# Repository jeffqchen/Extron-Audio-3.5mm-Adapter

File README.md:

# Extron Audio 3.5mm Adapter

This is an 3.5mm audio input/output adapter for the Extron switches. It conforms to the circuit design of the official CSM6 adapter to enable correct audio levels when balanced audio is adapted to unbalanced audio through a 3.5mm jack.

-----------
## Parts

- [PCB](https://oshpark.com/shared_projects/oJI7PVwu)

- Terminal Plug - 5 pin, 3.5mm pitch, right angle, through-hole - [Link](https://github.com/jeffqchen/JeffParts/blob/main/Connectors/Phoenix%20Terminal%20Connector/Female%20PCB/info.md)

- Horizontal 3.5mm Headphone Jack - [Link](https://github.com/jeffqchen/JeffParts/blob/main/Connectors/3.5mm%20Audio%20Jack/Horizontal%203-Pin%20PCB/info.md)

- M2x12mm screw and hex nut - [Link](https://github.com/jeffqchen/JeffParts/blob/main/Parts/M2%20M3%20Hex%20Screw%20%26%20Nut/info.md)

- 2x Resistors 1K Ohm - SMD 0805/0603 OR through-hole 1/4W

- 3D Printed Shell

-----------
## 3D Printing The Shell

Print "Shell.stl" and "Stopper.stl".*

Print the shell sideways, without support.

Print the stopper standing, with the screw hole vertical.

***Note:** for Extron devices with an audio port that's flush with the shell (such as the RGB series), please use the shell called "Shell Flush.stl". The normal one does not seat properly and the connection will be loose.

-----------
## Assembly

Solder all the components onto the PCB. Trim the extruding leads on the bottom as much as possible, but perfection is not required.

Slide the PCB assembly into the 3D printed shell from the rear opening. Push it all the way in. Then slide the printed stopper piece into the center cavity. Then secure the entire assembly with the M2 screw and nut. DO NOT over-tighten the screw, or the shell might crack.

If you plan to use the adapters side-by-side on a CrossPoint switch, take a side cutter and cut off the two side walls of the terminal plug. This will ensure two adjacent plugs won't interfere with each other.

--------
Special Thanks

qwertymodo (for the schematics of the original adapter)
- https://qwertymodo.com/
- https://twitter.com/qwertymodo

--------
Shield: [![CC BY-SA 4.0][cc-by-sa-shield]][cc-by-sa]

This work is licensed under a
[Creative Commons Attribution-ShareAlike 4.0 International License][cc-by-sa].

[![CC BY-SA 4.0][cc-by-sa-image]][cc-by-sa]

[cc-by-sa]: http://creativecommons.org/licenses/by-sa/4.0/
[cc-by-sa-image]: https://licensebuttons.net/l/by-sa/4.0/88x31.png
[cc-by-sa-shield]: https://img.shields.io/badge/License-CC%20BY--SA%204.0-lightgrey.svg

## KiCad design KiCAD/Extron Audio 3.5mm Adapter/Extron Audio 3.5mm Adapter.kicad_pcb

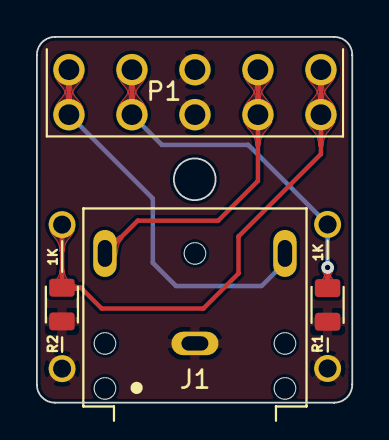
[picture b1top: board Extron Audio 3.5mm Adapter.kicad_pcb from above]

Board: 2 copper layers, 17.5 x 20.3 mm, 6 parts (0 on the bottom side), 5 nets.

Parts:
J1: 3.5mm_Jack_Horizontal; 3.5mm_jack_horizontal
P1: terminal_5pin; terminal_plug_5pin
R1, R2: 1K_SMD; Resistor_SMD_0805
T_R1, T_R2: 1K_SMD; Resistor_Through_Hole

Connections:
/GND: J1.1, P1.3, R1.2, R2.2, T_R1.2, T_R2.2
/L_Tip: J1.2, P1.1
/R_Ring: J1.3, P1.4
unnamed: P1.2, R1.1, T_R1.1
unnamed: P1.5, R2.1, T_R2.1

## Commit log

2021-10-22 Initial upload
2022-08-09 Change license type
2022-08-23 Add flush version
